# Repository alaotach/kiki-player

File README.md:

# Kiki-Player

## Project Overview

So basically this whole thing was built for a program by hackclub named fallout and I got an idea to build an mp3 player to replace spotify like good old times from a random youtube video titled "how to quit spotify" and I actually managed to pull it off. It's a fully custom PCB including a 3D case that plays music, has a touch sensitive click wheel.

## What's Inside This Folder

**PCB Files:**
- `kiki-player.kicad_sch` - The main schematic where everything's connected.
- `kiki-player.kicad_pcb` - The actual PCB layout with all components placed and routed.
- `Sample-BOM_JLCSMT.xlsx` - Bill of Materials with all the parts.

**3D Case Files:**
- `kiki-player-B_Cu.glb` / `kiki-player-B_Mask.glb` / `kiki-player-F_CuGlr` etc. - These are the individual layer exports from KiCad.
- `updated-pcb.step` - The 3D model of the PCB itself that I imported into Fusion 360 to design the case around it
- `kiki-player-case.stl` - The 3D model of the PCB case.

**Misc Files:**
- `.gorjob` files - Job queue files from Fusion 360 (not super important)
- `.csv` files - Component positioning data and BOM exports

## The Files You Actually Need

**To Manufacture the PCB:**
1. `kiki-player.kicad_pcb` - Send this to JLCPCB (export as gerbers first)
2. `Sample-BOM_JLCSMT.xlsx` - Upload this with your PCB order for parts + assembly
3. `kiki-player.kicad_sch` - Reference schematic if anything goes wrong

**For Reference:**
- `kiki-player.kicad_pro` - Open this in KiCad if you want to modify anything
- Schematic files - Check these if you want to understand how everything's wired

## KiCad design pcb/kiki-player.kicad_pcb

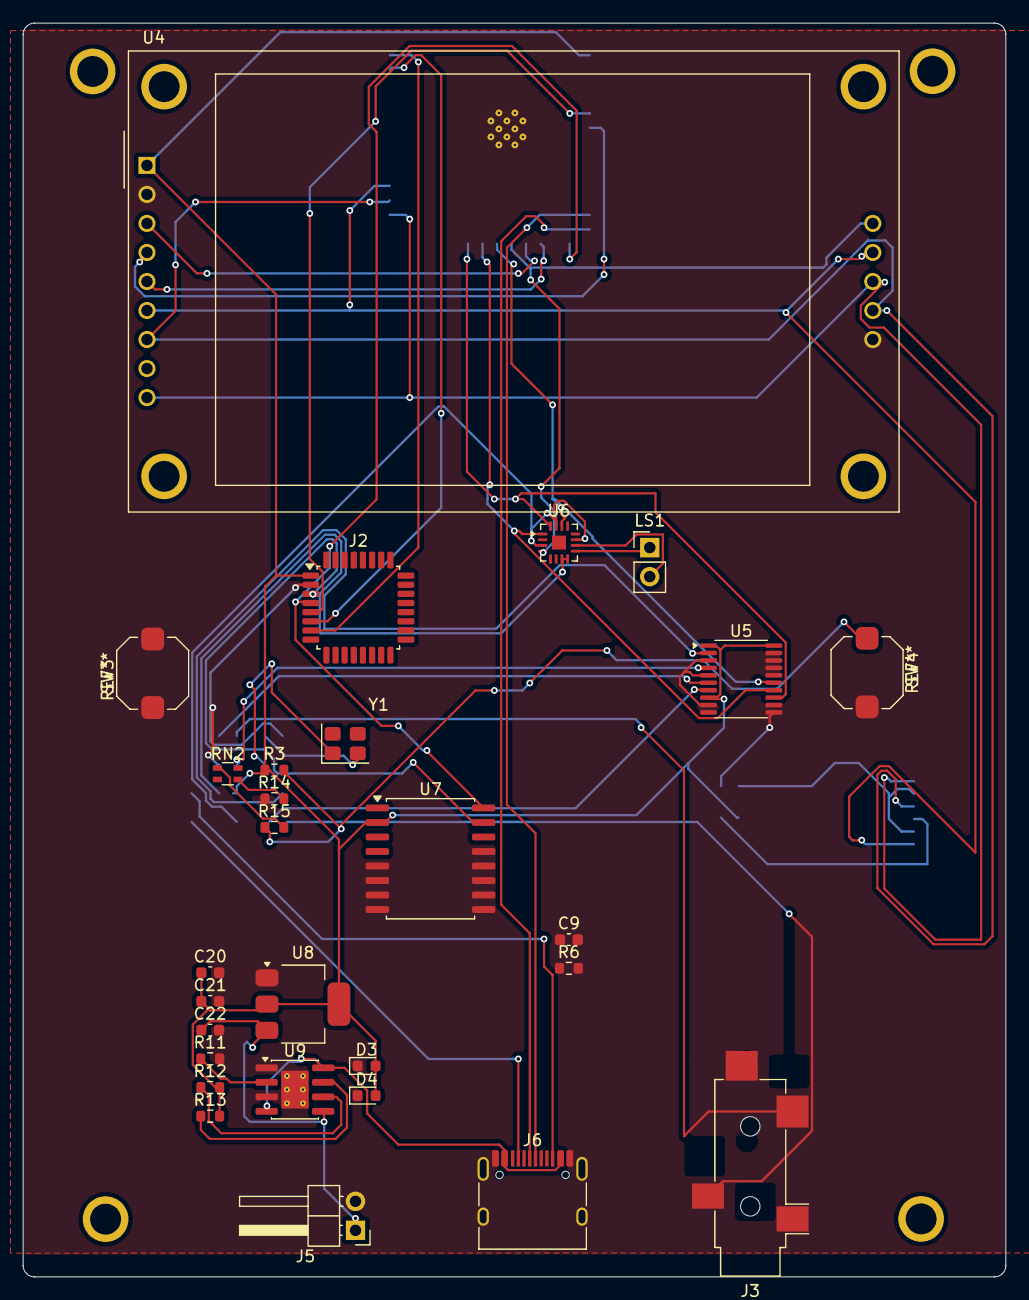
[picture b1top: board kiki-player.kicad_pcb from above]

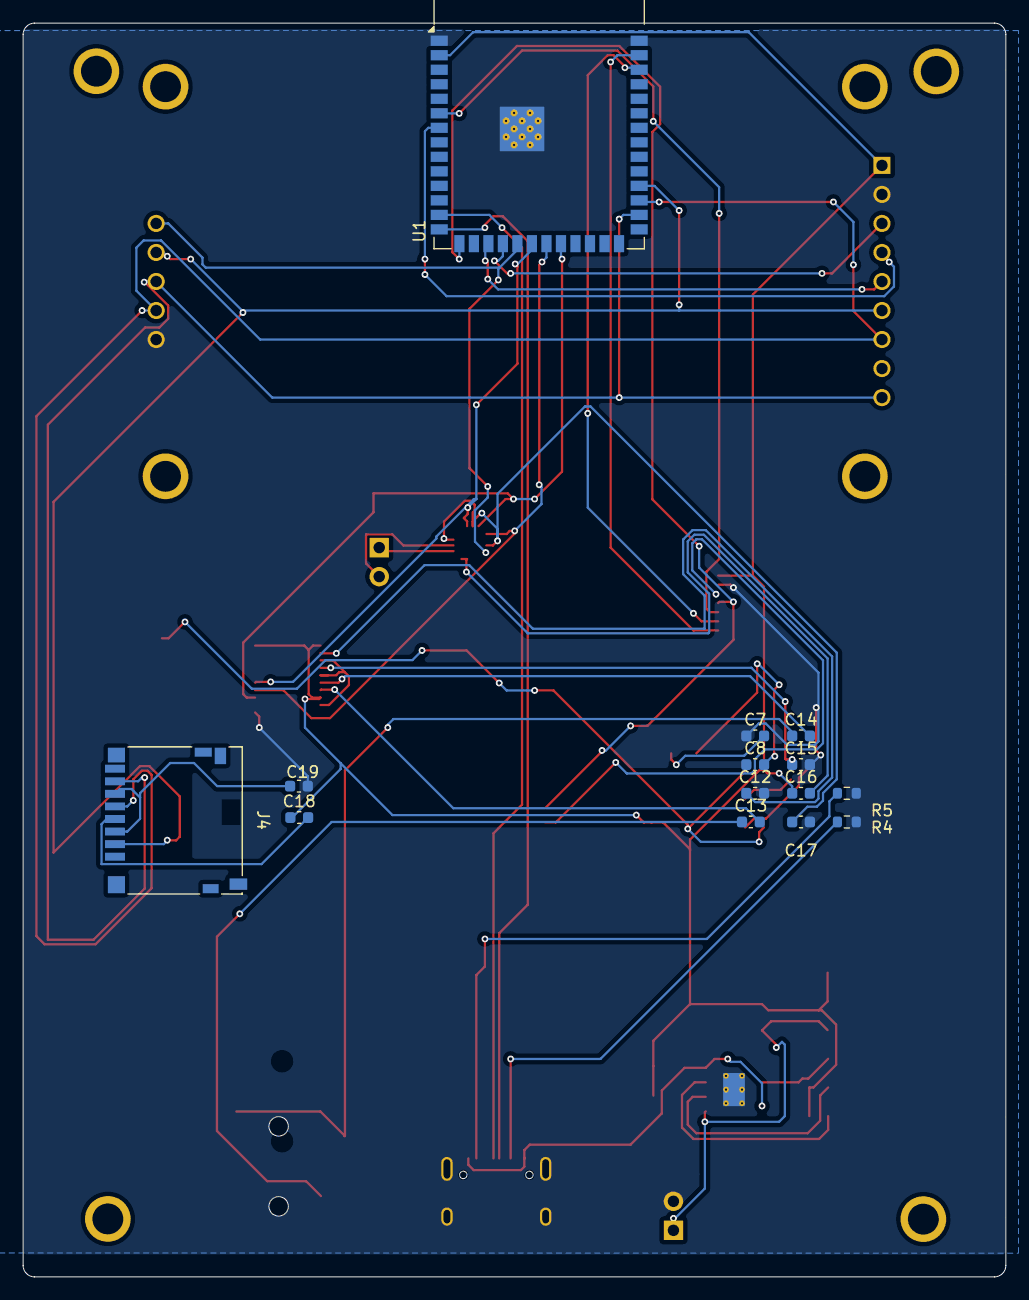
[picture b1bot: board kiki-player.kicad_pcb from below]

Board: 2 copper layers, 86.0 x 109.7 mm, 42 parts (14 on the bottom side), 42 nets.

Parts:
C7, C8: 12pF; C_0603_1608Metric
C9, C16, C17, C18, C19, C21: 100nF; C_0603_1608Metric
C12, C13, C14, C15, C20, C22: 10uF; C_0603_1608Metric
D3, D4: LED; LED_0603_1608Metric
J2: Conn_01x28_Socket; TQFP-32_7x7mm_P0.8mm
J3: AudioPlug3; Jack_3.5mm_CUI_SJ-3524-SMT_Horizontal
J4: SD_Card_Device; microSD_HC_Hirose_DM3D-SF
J5: Conn_02x01; PinHeader_1x02_P2.54mm_Horizontal
J6: USB_C_Receptacle_USB2.0_16P; USB_C_Receptacle_HRO_TYPE-C-31-M-12
LS1: Speaker; PinHeader_1x02_P2.54mm_Vertical
R3, R6, R12, R13: 10k; R_0603_1608Metric
R4, R5: 5.1k; R_0603_1608Metric
R11: 1.2k; R_0603_1608Metric
R14, R15: 100k; R_0603_1608Metric
RN2: VoltageDivider; R_Array_Convex_2x0603
SW3, SW4: SW_Push; SW_Push_1TS009xxxx-xxxx-xxxx_6x6x5mm
U1: ESP32-S3-WROOM-1
U4: CR2013-MI2120
U5: PCM5102A; TSSOP-20_4.4x6.5mm_P0.65mm
U6: MAX98357A; TQFN-16-1EP_3x3mm_P0.5mm_EP1.23x1.23mm
U7: DS3231M; SOIC-16W_7.5x10.3mm_P1.27mm
U8: AMS1117-3.3; SOT-223-3_TabPin2
U9: TP4056-42-ESOP8; SOIC-8-1EP_3.9x4.9mm_P1.27mm_EP2.41x3.3mm_ThermalVias
Y1: Crystal; Crystal_SMD_3225-4Pin_3.2x2.5mm

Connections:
+3V3: C16.1, C18.1, C20.1, C21.1, D3.2 (A), D4.2 (A), J2.1 (VDD), R3.1, R12.2, R13.2, U1.2 (3V3), U4.1 (VCC), U5.1 (CPVDD), U5.8 (AVDD), U5.20 (DVDD), U7.2 (VCC), U8.2 (VO)
/CHG: J2.7 (CHG), U1.39 (IO1)
/CLK: J4.5 (CLK), U1.29 (IO36), U4.7 (SCK), U4.13 (SD_SCK)
/CMD: J4.2 (CMD), U1.30 (IO37), U4.6 (MOSI), U4.11 (SD_MOSI)
/CS: U1.18 (IO10), U4.3 (~CS)
/D+: J6.A6 (D+), U1.14 (USB_D+)
/D-: J6.A7 (D-), U1.13 (USB_D-)
/DAT0: J4.7 (DAT0), U1.28 (IO35), U4.9 (MISO), U4.12 (SD_MISO)
/DIN: U1.21 (IO13), U5.14 (DIN), U6.1 (DIN)
/D/C: U1.17 (IO9), U4.5 (D/~C)
/GPIO14: U1.22 (IO14), U5.13 (BCK), U6.16 (BCLK)
/LRCK: U1.20 (IO12), U5.15 (LRCK), U6.14 (LRCLK)
/RESET: U1.7 (IO7), U4.4 (RESET)
/RESETMGC: J2.5 (RESET), U1.6 (IO6)
/RING: C13.2, U5.7 (OUTR)
/SCL: J2.4 (SCL), U1.15 (IO3), U7.16 (SCL)
/SDA: J2.3 (SDA), U7.15 (SDA)
/SD_CS: U1.19 (IO11), U4.10 (SD_CS), U6.4 (~SD_MODE)
/TOUCH: J2.6 (TOUCH), U1.38 (IO2)
/Tip: C14.2, U5.6 (OUTL)
GND: C7.1, C8.1, C9.1, C9.2, C12.2, C15.2, C17.2, C19.2, C20.2, C21.2, C22.2, D3.1 (K), D4.1 (K), J2.2 (GND), J3.S, J5.2, J6.A1 (GND), J6.A12 (GND), J6.B1 (GND), J6.B12 (GND), J6.SH (SHIELD), R4.2, R5.2, R6.1, R6.2, R11.2, R14.1, SW3.1, SW3.2, SW4.2 (2_2), U1.1 (GND), U1.40 (GND), U1.41 (GND), U4.2 (GND), U4.14 (FLASH_CD), U5.3 (CPGND), U5.5 (VNEG), U5.9 (AGND), U5.10 (DEMP), U5.11 (FLT), U5.12 (SCK), U5.16 (FMT), U5.17 (XSMT), U5.18 (LDOO), U5.19 (DGND), U7.5 (GND), U7.6 (GND), U7.7 (GND), U7.8 (GND), U7.9 (GND), U7.10 (GND), U7.11 (GND), U7.12 (GND), U7.13 (GND), U8.1 (GND), U9.1 (TEMP), U9.3 (GND), U9.9 (EPAD)
unnamed: C7.2, Y1.2
unnamed: C8.2, Y1.1
unnamed: C13.1, J3.R
unnamed: C14.1, J3.T
unnamed: C16.2, U6.7 (VDD), U6.8 (VDD)
unnamed: C17.1, U6.3 (GND), U6.11 (GND), U6.15 (GND)
unnamed: C19.1, J4.3 (VSS), J4.6 (VSS)
unnamed: C18.2, J4.4 (VDD)
unnamed: J6.A5 (CC1), R5.1
unnamed: J6.B5 (CC2), R4.1
unnamed: R14.2, RN2.3
unnamed: R15.2, RN2.1
unnamed: C15.1, U5.4 (CAPM)
unnamed: C12.1, U5.2 (CAPP)
unnamed: LS1.2, U6.10 (OUTN)
unnamed: LS1.1, U6.9 (OUTP)
unnamed: R11.1, U9.2 (PROG)
unnamed: R13.1, U9.7 (~CHRG)
unnamed: R12.1, U9.6 (~STDBY)
VBAT: C22.1, J5.1, U8.3 (VI), U9.5 (BAT)
VBUS: J6.A4 (VBUS), J6.A9 (VBUS), J6.B4 (VBUS), J6.B9 (VBUS), U9.4 (V_{CC}), U9.8 (CE)

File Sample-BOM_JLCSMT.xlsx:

Comment | Designator | Footprint | Qty | Unit Price | Total Price | URL
100nF | C21, C9, C18, C19, C17, C16 | Capacitor_SMD:C_603_1608Metric | 6 | 0.01 | 0.06 | https://projectpoint.in/index.php?route=product/product&prod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
10uF | C20, C22, C14, C15, C13, C12 | Capacitor_SMD:C_603_1608Metric | 6 | 2.5999999999999999E-2 | 0.156 | https://projectpoint.in/index.php?route=product%2Fproduct&pr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
5.1k Ohm | R5, R4 | Resistor_SMD:R_0603_1608Metric | 2 | 0.01 | 0.02 | https://projectpoint.in/index.php?route=product%2Fproduct&pr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
10k Ohm | R13, R6, R3, R14 | Resistor_SMD:R_0603_1608Metric | 4 | 0.01 | 0.04 | https://projectpoint.in/index.php?route=product%2Fproduct&pr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
100k Ohm | R14, R15 | Resistor_SMD:R_0603_1608Metric | 2 | 0.01 | 0.02 | https://projectpoint.in/index.php?route=product%2Fproduct&pr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
PCM5102A | U5 | Package_SO:TSSOP-20_4.4x6.5mm_P0.65mm | 1 | 1.84 | 1.84 | https://robu.in/product/weact-studio-i2s-speaker-module-pcm5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
DS3231M | U7 | Package_SO:SOIC-16W_7.5x10.3mm_P1.27mm | 1 | 1.76 | 1.76 | https://www.electropi.in/ds3231-rtc-module-india?gad_source=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
SW_PUSH | SW3, SW4 | Button_Switch_SMD:SW_Push_1TS009xxxx-xxxx-xxxx_6x6x5mm | 2 | 3.7999999999999999E-2 | 7.5999999999999998E-2 | https://www.electropi.in/push-button-switch-2-pin-5mm?gad_so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
Speaker | LS1 | Connector_PinHeader_2.54mm:PinHeader_1x02_p2.54mm_Vertical | 1 | 1.58 | 1.58 | https://robu.in/product/smartelex-digital-speaker-module/
MGC3130-I/MQ | J2 | Package_QFP:TQFP-32_7x7mm_P0.8mm | 1 |  | 1
MAX98357A | U6 | Package_DFN_QFN:TQFN-16-1EP_3x3mm_P0.5mm_EP1.23x1.23mm | 1 | 4.68 | 4.68 | https://www.amazon.in/Oceanlabz-MAX98357A-Amplifier-Micropho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
SD_CARD_DEVICE | J4 | Connector_Card:microSD_HC_Hirose_DM3D-SF | 1 | 2.5099999999999998 | 2.5099999999999998 | https://in.element14.com/hirose-hrs/dm3at-sf-pejm5-40/connec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
AudioPlug3 | J3 | Connector_Audio:Jack_3.5mm_CUI_SJ-3524-SMT_Horizontal | 1 | 0.13 | 0.13 | https://robu.in/product/audio-jack-pj311-3-5mm-female-connec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
Conn_02x01 | J5 | Connector_PinHeader_2.54mm:PinHeader_1x02_p2.54mm_Horizontal | 1 |  | 1
AMS1117-3.3 | U8 | Package_TO_SOT_SMD:SOT-223-3_TabPin2 | 1 | 7.2999999999999995E-2 | 7.2999999999999995E-2 | https://robu.in/product/ams1117-3-3v-1a-sot-223-voltage-regu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
TP4056-42-ESOP8 | U9 | Package_SO:SOIC-8-1EP_3.9x4.9mm_P1.27mm_EP2.41x3.3mm_ThermalVias | 1 | 0.33 | 0.33 | https://robu.in/product/tp4056-1a-li-ion-battery-charging-bo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
LED | D3, D4 | LED_SMD:LED_0603_1608Metric | 2 | 0.01 | 0.02
CR2013-MI2120 | U4 | Display:CR2013-MI2120 | 1 | 2.6 | 2.6 | https://www.electropi.in/1.8-inch-tft-lcd-module-128x160-with-4-io
ESP32-S3-WROOM-1 | U1 | RF_Module:ESP32-s3-WROOM-1 | 1 | 3.86 | 3.86 | https://www.electropi.in/espressif-esp32-s3-wroom-1-n4r8-mod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
Crystal | Y1 | Crystal:Crystal_SMD_3225-4Pin_3.2x2.5mm | 1 | 0.22 | 0.22 | https://robu.in/product/ysx321sl-24mhz-12pf-10ppm-4pins-smd-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
1.2k Ohm | R11, R12 | Resistor_SMD:R_0603_1608Metric | 2 | 0.01 | 0.02
Voltage Devider | RN2 | Resistor_SMD:R_Array_Convex_2x0603 | 1 | 0.01 | 0.01
12pF | C7, C8 | Capacitor_SMD:C_603_1608Metric | 2 | 0.01 | 0.02
1000 mAh battery |  |  | 1 | 4.2 | 4.2 | https://robu.in/product/wly394058-1000mah-3-7v-single-cell-r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
 |  |  |  |  | 26.224999999999998

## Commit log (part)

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2026-05-16 init firmware
2026-05-16 added config and pins def
2026-05-16 added app state def
2026-05-16 display init
2026-05-16 added audio setup play pause playing etc and in display i added starting boot text and error msgs
2026-05-16 added audio net/prev track shuffle repeat
2026-05-16 sdcard conf, scan dir for mp3s
2026-05-16 added rtc
2026-05-16 battery stats
2026-05-17 input events handling
2026-05-17 minimal ui
2026-05-17 update main.cpp to include and setup all the components
2026-05-17 fix submit
2026-05-17 fix submit readme
2026-06-12 Rename lala.step to pcb.step
2026-06-14 Rename kiki-player-case.f3d to kiki-player-case.f3d
2026-06-14 Rename kiki-player-case.step to kiki-player-case.step
